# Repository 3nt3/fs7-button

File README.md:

# FS7 Grip Emulator

Emulates an FS7 Grip for having a second place where user buttons can be reached.

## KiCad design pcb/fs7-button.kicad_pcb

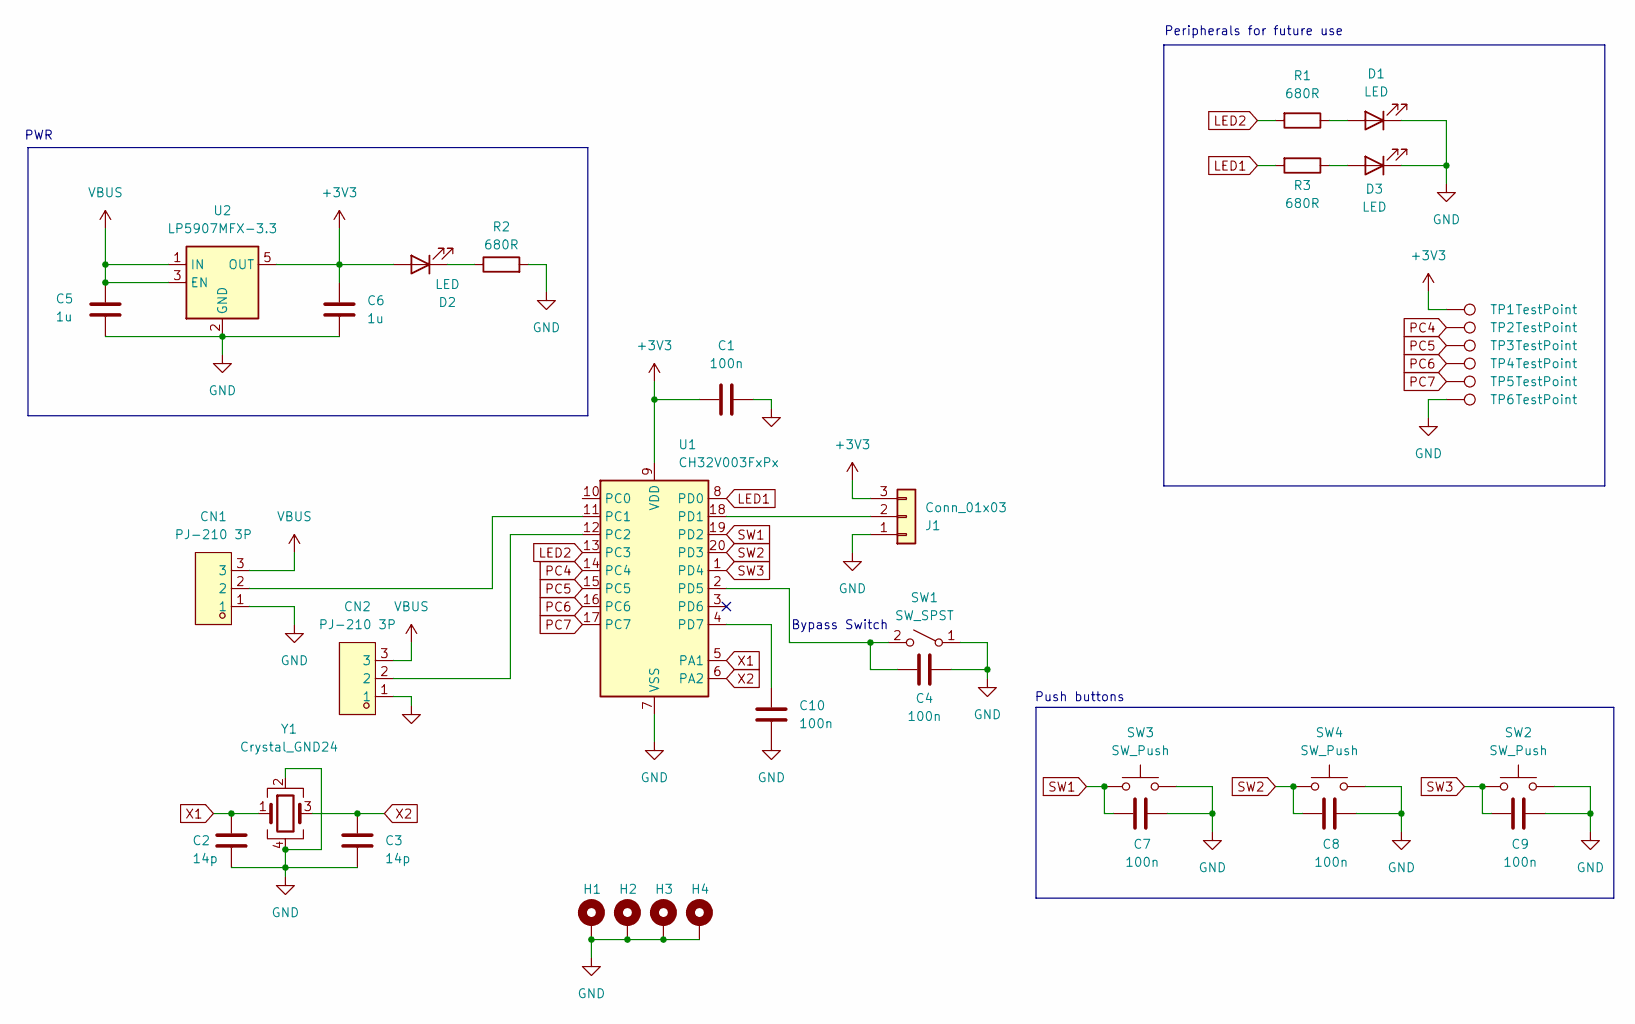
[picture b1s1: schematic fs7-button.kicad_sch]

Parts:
C1, C4, C7, C8, C9, C10: 100n; C_0603_1608Metric_Pad1.08x0.95mm_HandSolder
C2, C3: 14p; C_0603_1608Metric_Pad1.08x0.95mm_HandSolder
C5, C6: 1u; C_0603_1608Metric_Pad1.08x0.95mm_HandSolder
CN1, CN2: PJ-210 3P; AUDIO-TH_PJ-210-3P; LCSC Part C668602
D1, D2, D3: LED; LED_0603_1608Metric_Pad1.05x0.95mm_HandSolder
H1, H2, H3, H4: MountingHole_Pad; MountingHole_2.2mm_M2_Pad_Via
J1: Conn_01x03; PinHeader_1x03_P2.54mm_Vertical
R1, R2, R3: 680R; R_0603_1608Metric_Pad0.98x0.95mm_HandSolder
SW1: SW_SPST; SW-TH_SK12D07VG5-1
SW2, SW3, SW4: SW_Push; SW-SMD_4P-L5.1-W5.1-P3.70-LS6.5-TL_H1.5
TP1, TP2, TP3, TP4, TP5, TP6: TestPoint; TestPoint_Pad_D1.5mm
U1: CH32V003FxPx; TSSOP-20_4.4x6.5mm_P0.65mm
U2: LP5907MFX-3.3; SOT-23-5
Y1: Crystal_GND24; Crystal_SMD_3225-4Pin_3.2x2.5mm

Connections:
+3V3: C1.1, C6.1, D2.2 (A), J1.3, TP1.1, U1.9 (VDD), U2.5 (OUT)
GND: C1.2, C2.2, C3.2, C4.1, C5.2, C6.2, C7.2, C8.2, C9.2, C10.2, CN1.1, CN2.1, D1.1 (K), D3.1 (K), H1.1, H2.1, H3.1, H4.1, J1.1, R2.2, SW1.1 (A), SW2.2, SW3.2, SW4.2, TP6.1, U1.7 (VSS), U2.2 (GND), Y1.2, Y1.4
LED1: R3.2, U1.8 (PD0)
LED2: R1.2, U1.13 (PC3)
unnamed: D1.2 (A), R1.1
unnamed: D2.1 (K), R2.1
unnamed: D3.2 (A), R3.1
unnamed: J1.2, U1.18 (PD1)
unnamed: C4.2, SW1.2 (B), U1.2 (PD5)
unnamed: CN1.2, U1.11 (PC1)
unnamed: CN2.2, U1.12 (PC2)
unnamed: C10.1, U1.4 (PD7)
PC4: TP2.1, U1.14 (PC4)
PC5: TP3.1, U1.15 (PC5)
PC6: TP4.1, U1.16 (PC6)
PC7: TP5.1, U1.17 (PC7)
SW1: C7.1, SW3.1, U1.19 (PD2)
SW2: C8.1, SW4.1, U1.20 (PD3)
SW3: C9.1, SW2.1, U1.1 (PD4)
VBUS: C5.1, CN1.3, CN2.3, U2.1 (IN), U2.3 (EN)
X1: C2.1, U1.5 (PA1), Y1.1
X2: C3.1, U1.6 (PA2), Y1.3

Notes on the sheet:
Bypass Switch
Push buttons
Peripherals for future use
PWR

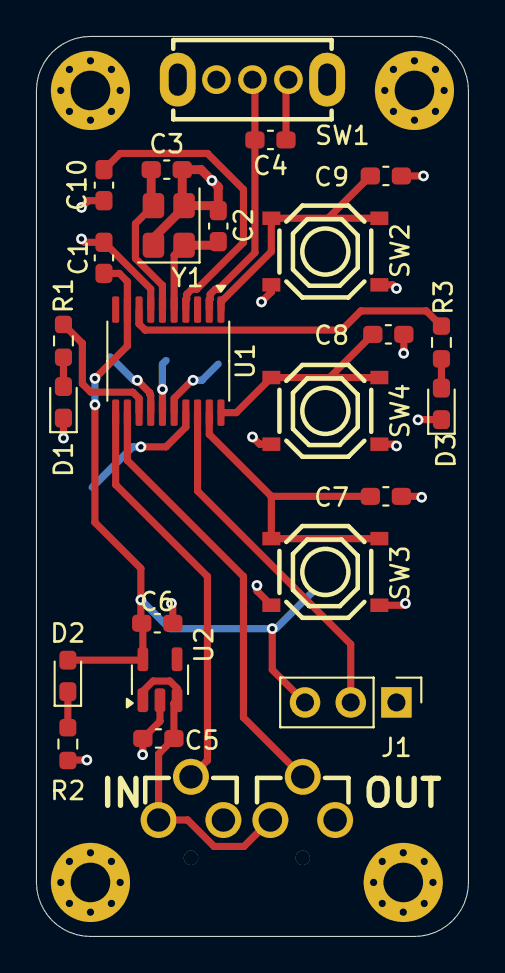
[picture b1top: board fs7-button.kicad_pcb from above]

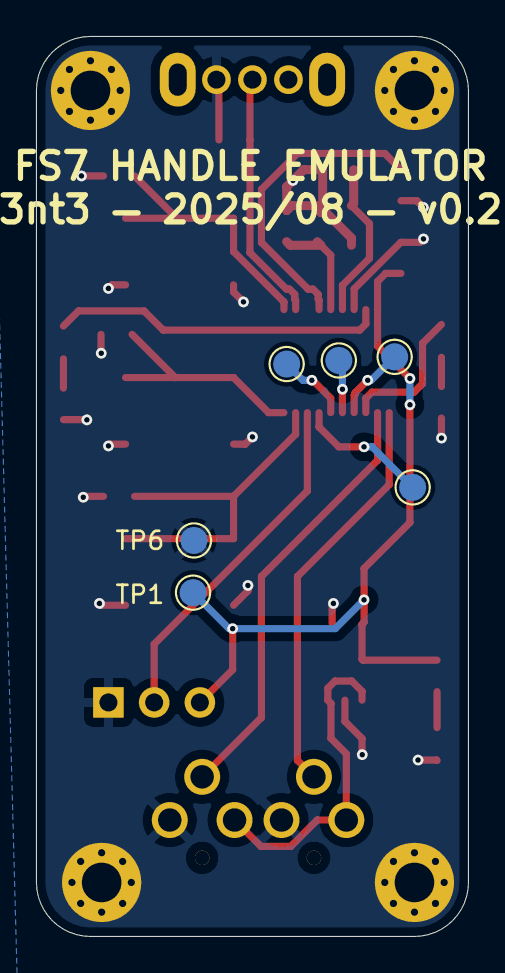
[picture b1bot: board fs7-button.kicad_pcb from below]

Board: 2 copper layers, 24.0 x 50.0 mm, 36 parts (6 on the bottom side), 22 nets.

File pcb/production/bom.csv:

Designator,Footprint,Quantity,Value,LCSC Part #
"3V3, GND, TP2, TP3, TP4, TP5",TestPoint_Pad_D1.5mm,6,TestPoint,
"C1, C4, C7, C8, C9",0603,5,100n,
"C2, C3",0603,2,14p,
"C5, C6",0603,2,1u,
"CN1, CN2",AUDIO-TH_PJ-210-3P,2,PJ-210 3P,C668602
"D1, D2, D3",0603,3,LED,
J1,PinHeader_1x03_P2.54mm_Vertical,1,Conn_01x03,
"R1, R2, R3",0603,3,680R,
SW1,SW-TH_SK12D07VG5-1,1,SW_SPST,
"SW2, SW3, SW4",SW-SMD_4P-L5.1-W5.1-P3.70-LS6.5-TL_H1.5,3,SW_Push,
U1,TSSOP-20_4.4x6.5mm_P0.65mm,1,CH32V003FxPx,
U2,SOT-23-5,1,LP5907MFX-3.3,
Y1,Crystal_SMD_3225-4Pin_3.2x2.5mm,1,Crystal_GND24,

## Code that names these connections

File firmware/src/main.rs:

#![no_std]
#![no_main]
#![feature(type_alias_impl_trait)]
#![feature(impl_trait_in_assoc_type)]
#![feature(riscv_ext_intrinsics)]

use ch32_hal::gpio::OutputOpenDrain;
use ch32_hal::println;
use defmt::info;
use embedded_hal::digital::InputPin;
use hal::delay::Delay;
use hal::gpio::{Input, Level, Output, Pull};

use crate::lanc::ButtonCmd;

use {ch32_hal as hal, panic_halt as _};

/// LANC module
///
/// [LANC](https://en.wikipedia.org/wiki/LANC) is a bidirectional serial open collector communication port, where two devices can communicate with each other. The camcorder or still video camera is able to receive commands and sends back its status.
/// A write up of various commands and the protocol in general has been attempted by
/// [boehmel.de](https://www.boehmel.de/lanc.htm), even though none of the commands used by my
/// [PXW-FS7](https://pro.sony/ue_US/products/handheld-camcorders/pxw-fs7) are listed there lol.
///
/// # Example
/// ```rust
/// use ch32_hal::{self as hal, gpio::{OutputOpenDrain, Level}};
///
/// let mut camera_io = OutputOpenDrain::new(p.PC2, Level::High, ch32_hal::gpio::Speed::High);
///
/// lanc::write_button(&mut camera_io, lanc::ButtonCmd::User4, &mut delay);
/// ```
pub mod lanc;

#[qingke_rt::entry]
fn main() -> ! {
    hal::debug::SDIPrint::enable();
    let mut config = hal::Config::default();
    config.rcc = hal::rcc::Config::SYSCLK_FREQ_48MHZ_HSE;
    let p = hal::init(config);

    let mut delay = Delay;

    let mut led1 = Output::new(p.PD0, Level::Low, Default::default());
    let mut led2 = Output::new(p.PC3, Level::Low, Default::default());

    let btn1 = Input::new(p.PD4, Pull::Up);
    let btn2 = Input::new(p.PD3, Pull::Up);
    let btn3 = Input::new(p.PD2, Pull::Up);
    let switch = Input::new(p.PD5, Pull::Up);

    let mut camera_io = OutputOpenDrain::new(p.PC2, Level::High, ch32_hal::gpio::Speed::High);

    loop {
        if btn1.is_low() || btn2.is_low() || btn3.is_low() {
            led1.set_high();
            led2.set_high();
        } else {
            led1.set_low();
            led2.set_low();
        }

        if btn1.is_low() {
            info!("btn1 pressed");
            lanc::write_button(&mut camera_io, ButtonCmd::User4, &mut delay);
        }
        if btn2.is_low() {
            info!("btn2 pressed");
            lanc::write_button(&mut camera_io, ButtonCmd::User5, &mut delay);
        }
        if btn3.is_low() {
            info!("btn3 pressed");
            lanc::write_button(&mut camera_io, ButtonCmd::User6, &mut delay);
        }

        delay.delay_ms(10);
    }
}

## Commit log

2025-07-28 add abstractions
2025-07-28 i am living in fear to lose data so im pushing now
2025-07-28 WORKING PROTOTYPE!!!
2025-08-08 schematic
2025-08-14 some kind of version
2025-10-11 move firmware -> firmware-stm32, firmware-ch32v003 -> firmware
2025-10-12 make it workkkk
2025-10-14 wow i really need to commit more often
2025-10-14 remove old firmware
2025-10-14 add readme
2025-10-14 Implement more buttons
2025-10-14 add documentation
2025-10-14 add cutouts for cables and switch
2025-10-14 move pcb to correct place in assembly
2025-10-14 add clips
2025-10-14 add all clips
2025-10-14 make the clips fit
